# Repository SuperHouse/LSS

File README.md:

SuperHouse Light Switch Shield
==============================
Copyright 2018 SuperHouse Automation Pty Ltd  
www.superhouse.tv  

2-channel breakout for SuperHouse home automation light switches.

Each channel can connect to one light switch with up to 4 buttons.

Features:

 * 2 x RJ45 sockets.
 * Power selection between VIN and IOREF.
 * Prototyping area.

More information is available at:

  http://www.superhouse.tv/lss

INSTALLATION
------------
The design is saved as an EAGLE project. EAGLE PCB design software is
available from www.cadsoftusa.com free for non-commercial use. To use
this project download it and place the directory containing these files
into the "eagle" directory on your computer. Then open EAGLE and
navigate to the project.

DISTRIBUTION
------------
The specific terms of distribution of this project are governed by the
license referenced below.

LICENSE
-------
Licensed under the TAPR Open Hardware License (www.tapr.org/OHL).
The "license" folder within this repository also contains a copy of
this license in plain text format.

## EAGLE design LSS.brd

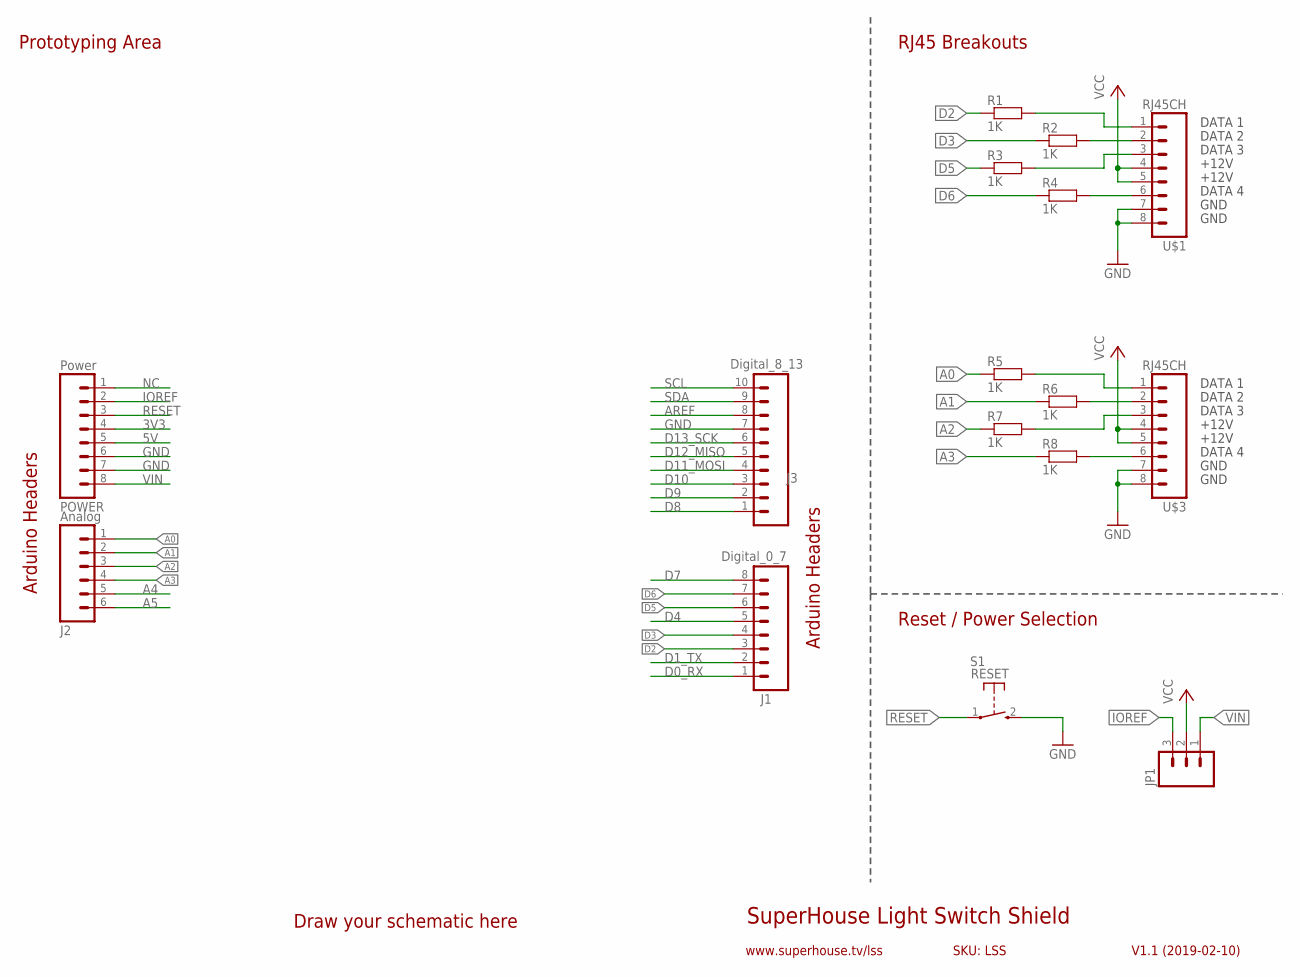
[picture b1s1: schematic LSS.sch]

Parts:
J1: Digital_0_7; 1X08
J2: Analog; 1X06
J3: Digital_8_13; 1X10
JP1: M03PTH; 1X03
POWER: Power; 1X08
R1, R2, R3, R4, R5, R6, R7, R8: 1K; 0603
S1: RESET; TACTILE_SWITCH_SMD_2PIN_TINY
U$1, U$3: RJ45CH

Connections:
3V3: POWER.4
5V: POWER.5
A0: J2.1, R5.1
A1: J2.2, R6.1
A2: J2.3, R7.1
A3: J2.4, R8.1
A4: J2.5
A5: J2.6
AREF: J3.8
D0_RX: J1.1
D1_TX: J1.2
D2: J1.3, R1.1
D3: J1.4, R2.1
D4: J1.5
D5: J1.6, R3.1
D6: J1.7, R4.1
D7: J1.8
D8: J3.1
D9: J3.2
D10: J3.3
D11_MOSI: J3.4
D12_MISO: J3.5
D13_SCK: J3.6
GND: J3.7, POWER.6, POWER.7, S1.2 (S), U$1.7, U$1.8, U$3.7, U$3.8
IOREF: JP1.3, POWER.2
unnamed: R1.2, U$1.1
unnamed: R2.2, U$1.2
unnamed: R3.2, U$1.3
unnamed: R4.2, U$1.6
unnamed: R5.2, U$3.1
unnamed: R6.2, U$3.2
unnamed: R7.2, U$3.3
unnamed: R8.2, U$3.6
NC: POWER.1
RESET: POWER.3, S1.1
SCL: J3.10
SDA: J3.9
VCC: JP1.2, U$1.4, U$1.5, U$3.4, U$3.5
VIN: JP1.1, POWER.8

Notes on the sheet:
SuperHouse Light Switch Shield
V1.1 (2019-02-10)
www.superhouse.tv/lss
SKU: LSS
Arduino Headers
DATA 1
DATA 2
DATA 3
DATA 4
+12V
GND
Prototyping Area
RJ45 Breakouts
Reset / Power Selection
Draw your schematic here

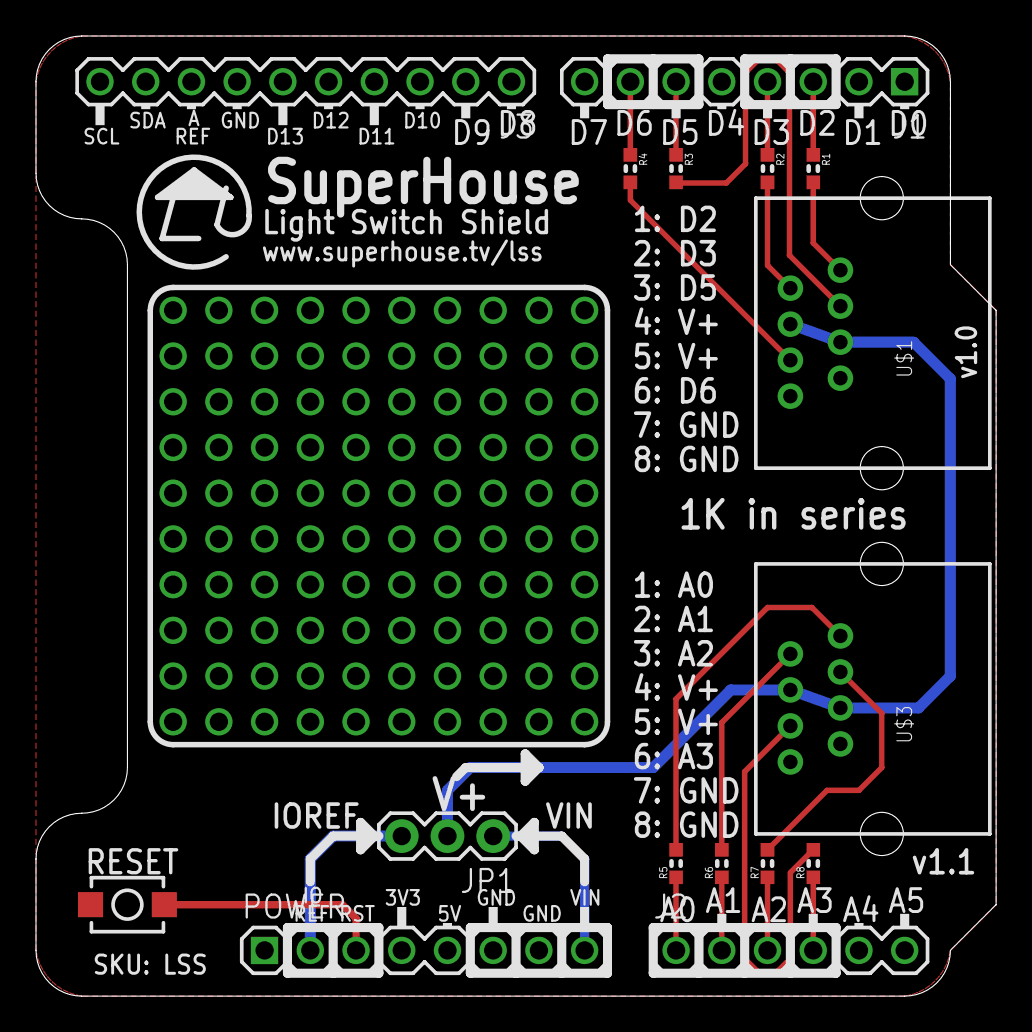
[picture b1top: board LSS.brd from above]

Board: 2 copper layers, 53.3 x 53.3 mm, 16 parts (0 on the bottom side), 21 nets.

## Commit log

2018-10-25 Initial project import
2019-02-10 Release v1.1 with D4 cleared to allow use on EtherTen

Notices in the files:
LSS.brd:
(C) 2019 SuperHouse Automation Pty Ltd
